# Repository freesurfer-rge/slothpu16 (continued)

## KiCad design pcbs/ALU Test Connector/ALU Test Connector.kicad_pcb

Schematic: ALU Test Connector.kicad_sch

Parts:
J1, J2: Conn_02x20_Odd_Even; PinHeader_2x20_P2.54mm_Vertical
J3: Conn_01x04; PinHeader_1x04_P2.54mm_Vertical
J4, J5, J6: TE-5530843-4-Mount
J7: Barrel_Jack_Switch; BarrelJack_Horizontal

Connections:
+5V: J3.1, J3.2, J4.B1, J5.B1, J6.B1, J7.1
/A0: J1.1, J4.A2, J5.A2, J6.A3
/A1: J1.2, J4.B2, J5.B2, J6.B3
/A2: J1.3, J4.A3, J5.A3, J6.A4
/A3: J1.4, J4.B3, J5.B3, J6.B4
/A4: J1.5, J4.A4, J5.A4, J6.A5
/A5: J1.6, J4.B4, J5.B4, J6.B5
/A6: J1.7, J4.A5, J5.A5, J6.A6
/A7: J1.8, J4.B5, J5.B5, J6.B6
/A8: J1.9, J4.A6
/A9: J1.10, J4.B6
/A10: J1.11, J4.A7
/A11: J1.12, J4.B7
/A12: J1.13, J4.A8
/A13: J1.14, J4.B8
/A14: J1.15, J4.A9
/A15: J1.16, J4.B9
/B0: J1.17, J4.A11, J5.A8, J6.A9
/B1: J1.18, J4.B11, J5.B8, J6.B9
/B2: J1.19, J4.A12, J5.A9, J6.A10
/B3: J1.20, J4.B12, J5.B9, J6.B10
/B4: J1.21, J4.A13, J5.A10, J6.A11
/B5: J1.22, J4.B13, J5.B10, J6.B11
/B6: J1.23, J4.A14, J5.A11, J6.A12
/B7: J1.24, J4.B14, J5.B11, J6.B12
/B8: J1.25, J4.A15
/B9: J1.26, J4.B15
/B10: J1.27, J4.A16
/B11: J1.28, J4.B16
/B12: J1.29, J4.A17
/B13: J1.30, J4.B17
/B14: J1.31, J4.A18
/B15: J1.32, J4.B18
/C0: J2.33, J4.A20, J5.A17, J6.A16
/C1: J2.34, J4.B20, J5.B17, J6.B16
/C2: J2.35, J4.A21, J5.A18, J6.A17
/C3: J2.36, J5.B18, J6.B17
/C4: J2.37, J5.A19, J6.A18
/C5: J2.38, J5.B19, J6.B18
/C6: J2.39, J5.A20, J6.A19
/C7: J2.40, J5.B20, J6.B19
/Carry_{Out}: J2.16, J6.B14
/Carry_{in}: J1.33, J6.A14
/~Add: J1.35, J6.A2
/~Compare: J1.34, J4.B21
/~NAND: J1.37, J5.A14
/~Sub: J1.36, J6.B2
/~XOR: J1.38, J5.B14
GND: J3.3, J3.4, J4.A22, J5.A22, J6.A22, J7.2

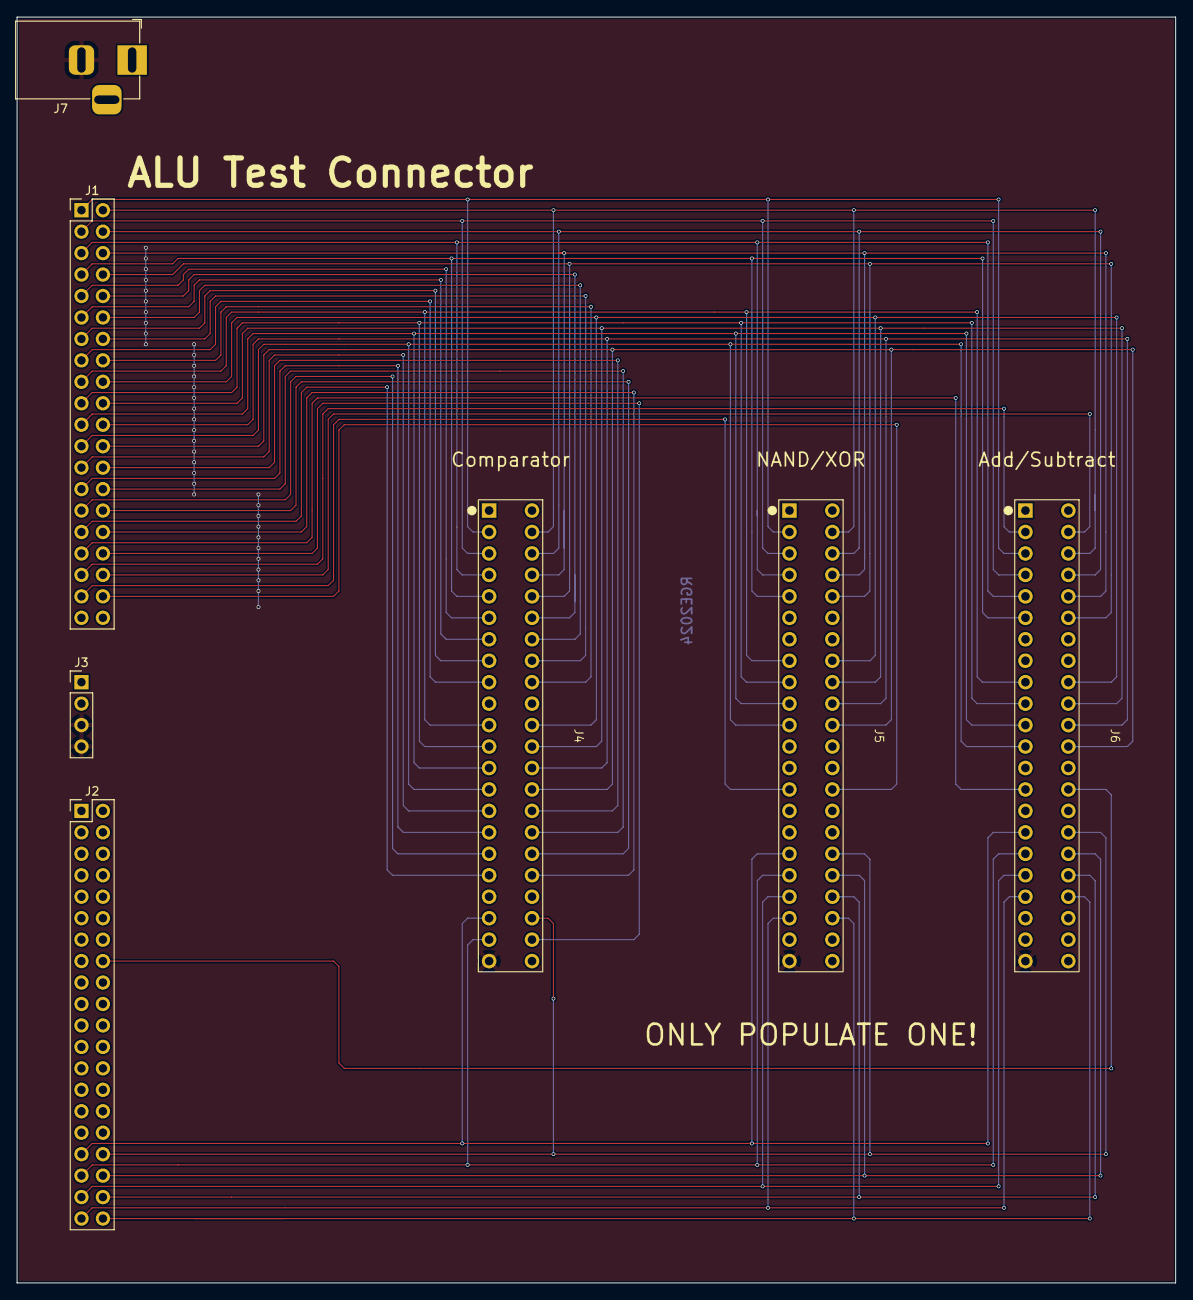
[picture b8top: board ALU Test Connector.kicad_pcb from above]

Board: 2 copper layers, 137.2 x 149.9 mm, 7 parts (0 on the bottom side), 49 nets.

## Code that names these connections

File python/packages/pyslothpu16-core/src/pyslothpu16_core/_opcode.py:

from enum import IntEnum, unique


@unique
class OpCode(IntEnum):
    ADD = 0
    SUB = 1
    COMPARE = 4
    NAND = 5
    XOR = 6
    BARREL = 7
    LOADB = 8
    LOADW = 9
    STOREB = 10
    STOREW = 11
    LOADPC = 12
    BRANCHZERO = 13
    HALT = 14
    SET = 15

    @classmethod
    def from_str(cls, value: str) -> "OpCode":
        for oc in OpCode:
            if value.lower() == oc.name.lower():
                return oc
        raise ValueError(f"Invalid opcode: {value}")


@unique
class Compare(IntEnum):
    EQUAL = 2
    LESSTHAN = 1
    GREATERTHAN = 4

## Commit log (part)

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2024-09-15 Very beginning
2024-09-15 Adding design rules
2024-09-16 Routing the actual registers
2024-09-18 Working on reset logic and some routing
2024-09-21 First draft of whole board
2024-09-21 Start a ReadMe
2024-09-21 Starting on test connector
2024-09-21 Routing
2024-09-22 Add order number mark
2024-09-24 Fix the reset logic....
2024-09-24 Fixing via sizes
2024-09-24 [Board] Register with Reset (#1)
    Add a board for a 16-bit register, with a reset line. Includes a test connector to the SlothPU tester board.
    Some notes:
    - Had to increase via size from the 'capabilities' page, since the minimum sizes cost more
    - I believe that the diodes (but not LEDs) were orientated backwards in the default placement. If I'm wrong, there will be an r1 board....
2024-10-19 Drafting connector
2024-10-19 Trying to get things working
2024-10-19 Initial tests...
2024-10-19 Need to be a bit more generous with times
2024-10-19 blacken
2024-10-20 Add notes to ReadMe
2024-10-20 Tester for Register with Reset (#2)
    Bring over the `tester_board.py` from [SlothPU](https://www.github.com/freesurfer-rge/slothpu/) and create tests of the Register with Reset board.
    ReadMe has been updated with notes from the testing.
2024-11-02 Addressing clock blocking issue
2024-11-02 Update connector board
2024-11-02 Starting to redo layout
2024-11-02 A little more editing
2024-11-02 Get buses routed
2024-11-02 Everything connected
2024-11-03 Prep for manufacture
2024-11-03 Revise the Register with Reset (#3)
    Updates to Register-with-Reset:
    - Convert to edge connector
    - Route clock through an 'AND' with the Reset line, so the clock doesn't block reset
    - Shrink the board somewhat by repositioning components
2024-11-09 Drafting
2024-11-10 Basic routing
2024-11-16 Splitting up tests, to isolate issue
2024-11-16 Adjust logic around reset calls
2024-11-16 Scatter in some more values
2024-11-16 Update Register with Reset tests (#4)
    Having some issues with the tests on the r1 board. Make some updates (which now pass, and appear to be working correctly), but reasons for behaviours observed are not entirely clear.
2024-11-17 Drafting a connector board
2024-11-17 No .DS_Store
2024-11-17 Ignore .DS_Store
2024-11-17 Final prep
2024-11-17 Incrementer (#5)
    Add a PCB (and associated test connector) for the incrementer. This will go on the Program Counter board, next to the Register-with-Reset board (which will be the program counter itself), and handle 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
2024-11-22 Starting barrel shifter
2024-11-23 Second row
2024-11-23 Starting to tidy up the LEDs
2024-11-23 Significant rethinking
2024-11-23 Remove old schematics
2024-11-24 Almost there...
2024-11-24 Finishing connection
2024-11-24 Starting on Register File
2024-11-24 Roughing out some layout
2024-11-24 Lots of thinking and routing
2024-11-27 Compaction
2024-11-28 Thinking, scheming, plotting
2024-11-28 Routing, routing, routing
2024-11-28 Routing.... first draft?
2024-11-28 Deal with islands
2024-11-29 Add in test connector
2024-11-29 Working on another connector
2024-11-30 Add test file
2024-11-30 Tester for Incrementer (#6)
    Add Python code for testing the incrementer board
2024-12-01 Missing wire
2024-12-01 Working on exclude from BOM etc.
2024-12-04 Minor fixes
2024-12-14 Starting on tester
2024-12-14 All tests etc.
2024-12-14 Trying the register file... things not working
2024-12-15 Starting work on Adder/Subtractor
2024-12-15 Getting the rest of the tests
2024-12-16 Add output buffer
2024-12-19 Indicator LEDs
2024-12-20 Starting on comparator
2024-12-20 Starting routing
2024-12-20 Capacitors for Adder/Subtractor
2024-12-20 Finish routing draft
2024-12-21 XOR/NAND board
2024-12-21 Add alternative power connector
2024-12-22 Running all checks etc.
2024-12-24 Further ALU units (#8)
    Three final units for the ALU:
    - Comparator (16-bit)
    - Adder/Subtracter (8-bit)
    - XOR/NAND (8-bit)
    There is also a single test connector board, which should be able to accept any of the boards (but only one at a time).
2024-12-27 Fix gitignore
2024-12-27 Adding an overview
2024-12-27 Expand the ReadMe a little
2024-12-27 More text
2024-12-27 Starting to lay out the instruction set
2024-12-27 [Doc] Getting started (#9)
    Start writing the documentation for SlothPU16. Doing this will unblock creation of the next set of boards, which will hold the various individual functions which I've been creating.
2024-12-27 Starting on connector
2024-12-27 Trying to figure out some routing. Not much success
2024-12-28 Some routing
2024-12-28 More connections, more routing
2024-12-28 Some more routes
2024-12-29 Connections and capacitors
2024-12-29 Starting on the connections...
2024-12-31 Further board tests (#10)
    Tests for the register file and barrel shifter
2025-01-01 Basic add tests
2025-01-01 Getting subtract tests working
2025-01-01 Enable everything
2025-01-01 Working on NAND and XOR
2025-01-01 Enable all tests
2025-01-01 Comparator testing
2025-01-01 Final 'off state' tweaks
2025-01-03 Thinking about Pi connections
2025-01-03 Don't destroy the Pi
2025-01-03 Completing initial wire-up
2025-01-03 Double checking
2025-01-04 Silkscreen
2025-01-04 Add barrel connector
2025-01-04 Add order number location
2025-01-11 [PCB] Pi Backplane (#12)
    A connector board, designed to link a Pi to the backplane. This will have two purposes:
    - Testing individual functional units (particularly the PC and ALU)
    - Acting as memory for the whole machine
    The core of the design are two banks of shift registers (one output, one input), which are connected to the backplane connector itself. The Pi sends data to the output shift registers, and reads from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
2025-01-19 Starting on the outputs... having trouble with the board
2025-01-19 Things _are_ working (so far)
2025-01-19 And the cycle bit
2025-01-19 Working on inputs... ugly
2025-01-19 Working on a proper test file
2025-01-19 Clock and Reset lines
2025-01-19 [Test] Pi Backplane (#13)
    Add a class for handling the Pi Backplane Connector board (in the `python-testing` directory for now), along with a test file (since the point of the board is that outputs also have connections to in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
    The re-ordering going on with the input registers is.... quite something.
2025-01-25 Getting started
2025-01-25 Adding the adder
2025-01-25 Working...
2025-01-25 Roughing out
2025-01-26 Fix indicators
2025-01-26 Refactor
2025-01-27 Working towards the connectors
2025-01-27 More experimental routing
2025-01-27 Thinking some more
2025-02-01 Add part number placer
2025-02-02 [PCB] ALU Carrier (#14)
    Create the ALU carrier, to hold the various individual boards which have been created so far.
2025-02-09 Drafting comparator test
2025-02-09 Get things working
2025-02-16 Adder and subtractor
2025-02-16 Bitwise operations
2025-02-16 Debugging & move enable operation
2025-03-02 Correcting barrel shifter
2025-03-02 Run checks
2025-03-09 Add the revision
2025-04-06 Fix for ALU Carrier (#16)
    Fix the connections to the barrel shifter. A copy/paste error had left these the same for both of the connectors, when one was supposed to have the inputs rotated by 8 steps.
    Also name the connectors on the silkscreen (closes #15 )
2025-04-16 Add in barrel shifter
2025-04-26 ALU Python Tests (#17)
    Tests of the whole ALU carrier board.
2025-04-26 Roughing a little more out
2025-04-27 Working on register selectors
2025-04-27 Expanding register file testing
2025-04-28 Expanding Register File testing (#18)
    Expand the register file tests a little, making sure that multiple 'static' values are correctly held. Also introduce a constant to replace a magic number.
2025-04-28 Thinking some things through
2025-04-28 Extra note
2025-04-28 Adding some more bits
2025-04-30 Starting to route
2025-05-03 Rethinking layout
2025-05-03 Thinking some routing
2025-05-05 More LEDs and routing
2025-05-10 Draft of final routing
2025-05-11 Adding mounting holes; thinking about needs
2025-05-11 Shrink board slightly
2025-05-14 Output buffers were a bad idea which were about to cause trouble
2025-05-14 Rerouting
2025-05-14 Add Active indicator
2025-05-16 [PCB] Register File Carrier (#19)
    Carrier board to combine four of the previously designed register files into a single bank of sixteen 16-bit registers.
2025-05-24 Drafting a test
2025-05-24 Debugging
2025-05-24 Fixing logic
2025-05-24 Use same inverter
2025-05-26 [PCB] Register File Carrier r01 (#21)
    Update the Register File Carrier to get the 'enable' logic correct. Had constructed an 'Active High' when 'Active Low' was required.
    Also should address #20 , standardising on a single part.
2025-06-04 Add one more value
2025-06-05 Figuring out main tests
2025-06-06 Enable all registers in test
2025-06-08 [Test] Test for Register Carrier (#22)
    Add a test file for the Register Carrier board.
2025-07-15 Starting the new project
2025-07-16 Writing up some notes
2025-07-16 Resizing sheet
2025-07-17 Starting to think about connections
2025-07-19 Some preliminary routing
2025-07-19 Thinking about more circuitry
2025-07-20 More schematic, more layout
2025-07-22 Add JLCJLCJLCJLC to back silkscreen
2025-07-25 Routing.... should be silkscreen and final adjustments next
2025-07-25 Some more LEDs and silkscreening
2025-07-25 Prepping for final check
2025-07-26 Think I had something backwards.... will recheck after
2025-07-26 Move JLC tracking number
2025-07-27 Add note on schematic
2025-07-27 [PCB] Program Counter (#23)
    Initial design of the program counter. Have added a markdown file to the docs which describes the operation.
2025-08-09 Starting manual testing
2025-08-09 Rounding out manual testing
2025-08-09 First checks with real board
2025-08-09 Next instruction
2025-08-09 Helps to set the right bus when branching
2025-08-09 Improve branching tests
2025-08-16 [Test] Tests for the Program Counter (#24)
    A small set of tests for the program counter board. We should be considering doing some refactoring of the tests.
2025-08-18 Starting to draft
2025-08-21 Tweaking schematic and basic routing
2025-08-21 Completing routing; needs silkscreen
2025-08-23 Preliminary final layout
2025-08-23 Add name, shrink board slightly
2025-08-27 Final check and add more silkscreen
2025-08-27 [PCB] Instruction Register (#25)
    Add the instruction register (also contains the 'SET' instruction). Note that it reads the new instruction on B bus, which is a possibly questionable decision.
2025-09-06 Doing a little refactoring
2025-09-06 Reformat
2025-09-07 Figure out timing issue
2025-09-07 [Test] Test for Instruction Register (#26)
    Tests of the Instruction Register (which also holds the 'Set' instruction). This refactors some code from other tests into `constants.py` and `utils.py`. These moves have not been fully tested.
    Also note that there needs to be a delay after completing a RESET, in order to allow the RC delays in the RwR logic to fully reset.
2025-09-13 Starting final part
2025-09-14 Adding silkscreen
2025-09-14 Refinements
2025-09-15 Add s/n marker
2025-09-15 [PCB] Backplane (#27)
    The backplane for connecting the various sub-assemblies together. Will actually need two of these put together, because it would be absurdly large otherwise.
2025-10-05 Drafting a simple script to ready for connection
2025-10-05 Draft first assembler program
2025-10-05 Starting to think about the assembler
2025-10-05 Have bug in computing instruction
2025-10-05 Working on assembler
2025-10-06 Fill rest of memory
2025-10-06 Drafting main loop
2025-10-06 Testing....
2025-10-07 Trying to write another program
2025-10-07 An additional register setter
2025-12-21 Extra output
2025-12-21 [Feature] Driver for SlothPU16 (#28)
    A Python program to run SlothPU16, supplying the clock signal and memory. This is a minimal implementation (in particular, the four memory related instructions are not yet implemented), with a handfu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
2025-12-22 Starting some more docs
2025-12-22 First paragraph
2025-12-22 More description
2025-12-22 Scribble, scribble
2025-12-22 Writing
2025-12-22 And something about the python scripts
2025-12-22 Round out some more text
2025-12-22 A little more for the main ReadMe
